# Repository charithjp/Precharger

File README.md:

# Precharger

This project will be a simple DC bus precharger for a 60V DC bus, controlled by an Arduino Nano. Detailed specs to follow.

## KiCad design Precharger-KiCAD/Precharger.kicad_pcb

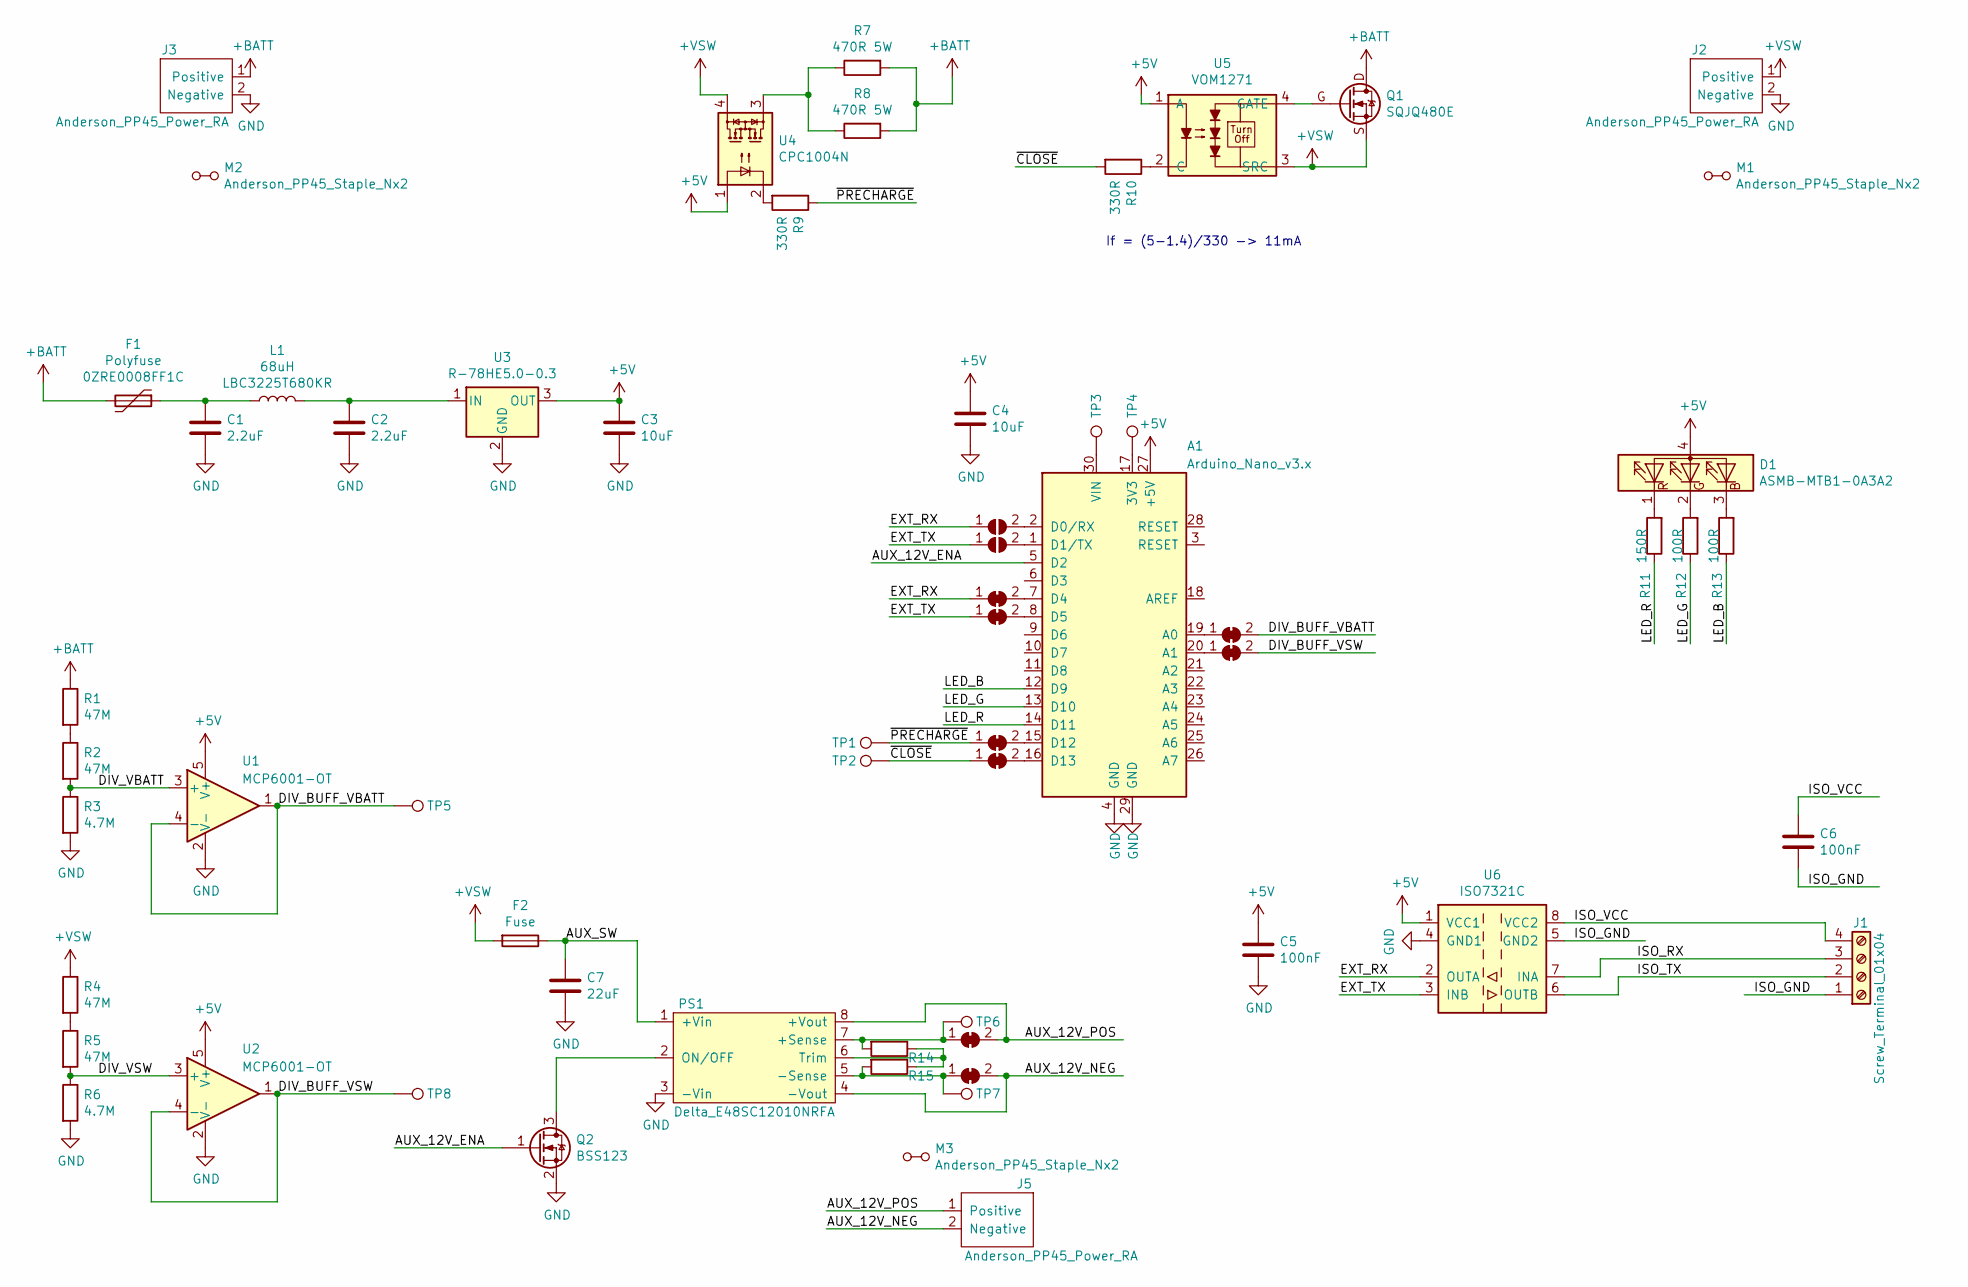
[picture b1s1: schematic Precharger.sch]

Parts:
A1: Arduino_Nano_v3.x; Arduino_Nano
C1, C2: 2.2uF; C_1210_3225Metric_Pad1.42x2.65mm_HandSolder
C3, C4: 10uF; C_0805_2012Metric_Pad1.15x1.40mm_HandSolder
C5, C6: 100nF; C_0805_2012Metric_Pad1.15x1.40mm_HandSolder
C7: 22uF; CP_Radial_D10.0mm_P5.00mm; Digikey PN 399-16572-ND
D1: ASMB-MTB1-0A3A2; LED_Avago_PLCC4_3.2x2.8mm_CW
F1: Polyfuse; Fuse_BelFuse_0ZRE0008FF_L8.3mm_W3.8mm; MFG_PN 0ZRE0008FF1C
F2: Fuse; Fuseholder_Clip-5x20mm_Schurter_0751_0052_Horizontal_Open
J1: Screw_Terminal_01x04; TerminalBlock_Phoenix_PT-1,5-4-3.5-H_1x04_P3.50mm_Horizontal
J2, J3, J5: Anderson_PP45_Power_RA; Anderson_Powerpole-45A-RA-Bottom-Pair
JP1, JP2: SolderJumper_2_Open; SolderJumper-2_P1.3mm_Open_RoundedPad1.0x1.5mm
JP3, JP4, JP5, JP6, JP7, JP8, JP9, JP10: SolderJumper_2_Bridged; SolderJumper-2_P1.3mm_Bridged2Bar_RoundedPad1.0x1.5mm
L1: 68uH; L_1210_3225Metric_Pad1.42x2.65mm_HandSolder; MFG_PN LBC3225T680KR
M1, M2, M3: Anderson_PP45_Staple_Nx2; Anderson_Powerpole-staple-Nx2
PS1: Delta_E48SC12010NRFA; Converter_DCDC_Delta_E48SC12010_THT
Q1: SQJQ480E; Vishay_PowerPAK_8x8L_Single
Q2: BSS123; SOT-23
R1, R2, R4, R5: 47M; R_0805_2012Metric_Pad1.15x1.40mm_HandSolder
R3, R6: 4.7M; R_0805_2012Metric_Pad1.15x1.40mm_HandSolder
R7, R8: 470R 5W; R_Axial_Power_L25.0mm_W9.0mm_P30.48mm
R9, R10: 330R; R_0805_2012Metric_Pad1.15x1.40mm_HandSolder
R11: 150R; R_0805_2012Metric_Pad1.15x1.40mm_HandSolder
R12, R13: 100R; R_0805_2012Metric_Pad1.15x1.40mm_HandSolder
R14, R15: TRIM_UP; R_0805_2012Metric_Pad1.15x1.40mm_HandSolder
TP1, TP2, TP3, TP4, TP5, TP6, TP7, TP8: TestPoint; TestPoint_Keystone_5010-5014_Multipurpose
U1, U2: MCP6001-OT; SOT-23-5_HandSoldering
U3: R-78HE5.0-0.3; Converter_DCDC_RECOM_R-78HB-0.5_THT
U4: CPC1004N; SOP-4_3.8x4.1mm_P2.54mm_CPC1004N
U5: VOM1271; SOP-4_4.57x4.92mm_P2.54mm_VOM1271
U6: ISO7321C; SOIC-8_3.9x4.9mm_P1.27mm

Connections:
+5V: A1.27 (+5V), C3.1, C4.1, C5.1, D1.4 (A), U1.5 (V+), U2.5 (V+), U3.3 (OUT), U4.1, U5.1 (A), U6.1 (VCC1)
+BATT: F1.2, J3.1 (Positive), Q1.D (Drain), R1.1, R7.2, R8.2
+VSW: F2.2, J2.1 (Positive), Q1.S (Source), R4.1, U4.4, U5.3 (SRC)
/AUX_12V_ENA: A1.5 (D2), Q2.1 (G)
/AUX_12V_NEG: J5.2 (Negative), JP10.2 (B), PS1.4 (-Vout)
/AUX_12V_POS: J5.1 (Positive), JP9.2 (B), PS1.8 (+Vout)
/AUX_SW: C7.1, F2.1, PS1.1 (+Vin)
/DIV_BUFF_VBATT: JP7.2 (B), TP5.1, U1.1, U1.4 (-)
/DIV_BUFF_VSW: JP8.2 (B), TP8.1, U2.1, U2.4 (-)
/DIV_VBATT: R2.2, R3.1, U1.3 (+)
/DIV_VSW: R5.2, R6.1, U2.3 (+)
/EXT_RX: JP1.1 (A), JP3.1 (A), U6.2 (OUTA)
/EXT_TX: JP2.1 (A), JP4.1 (A), U6.3 (INB)
/ISO_GND: C6.2, J1.1, U6.5 (GND2)
/ISO_RX: J1.3, U6.7 (INA)
/ISO_TX: J1.2, U6.6 (OUTB)
/ISO_VCC: C6.1, J1.4, U6.8 (VCC2)
/LED_B: A1.12 (D9), R13.1
/LED_G: A1.13 (D10), R12.1
/LED_R: A1.14 (D11), R11.1
/~CLOSE: JP6.1 (A), R10.2, TP2.1
/~PRECHARGE: JP5.1 (A), R9.1, TP1.1
GND: A1.4 (GND), A1.29 (GND), C1.2, C2.2, C3.2, C4.2, C5.2, C7.2, J2.2 (Negative), J3.2 (Negative), PS1.3 (-Vin), Q2.2 (S), R3.2, R6.2, U1.2 (V-), U2.2 (V-), U3.2 (GND), U6.4 (GND1)
unnamed: A1.1 (D1/TX), JP2.2 (B)
unnamed: A1.2 (D0/RX), JP1.2 (B)
unnamed: A1.7 (D4), JP3.2 (B)
unnamed: A1.8 (D5), JP4.2 (B)
unnamed: A1.15 (D12), JP5.2 (B)
unnamed: A1.16 (D13), JP6.2 (B)
unnamed: A1.17 (3V3), TP4.1
unnamed: A1.19 (A0), JP7.1 (A)
unnamed: A1.20 (A1), JP8.1 (A)
unnamed: A1.30 (VIN), TP3.1
unnamed: C1.1, F1.1, L1.1
unnamed: C2.1, L1.2, U3.1 (IN)
unnamed: D1.1 (RK), R11.2
unnamed: D1.2 (GK), R12.2
unnamed: D1.3 (BK), R13.2
unnamed: JP9.1 (A), PS1.7 (+Sense), R14.2, TP6.1
unnamed: JP10.1 (A), PS1.5 (-Sense), R15.2, TP7.1
unnamed: PS1.2 (ON/OFF), Q2.3 (D)
unnamed: PS1.6 (Trim), R14.1, R15.1
unnamed: Q1.G (Gate), U5.4 (GATE)
unnamed: R1.2, R2.1
unnamed: R4.2, R5.1
unnamed: R7.1, R8.1, U4.3
unnamed: R9.2, U4.2
unnamed: R10.1, U5.2 (C)

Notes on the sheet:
If = (5-1.4)/330 -> 11mA

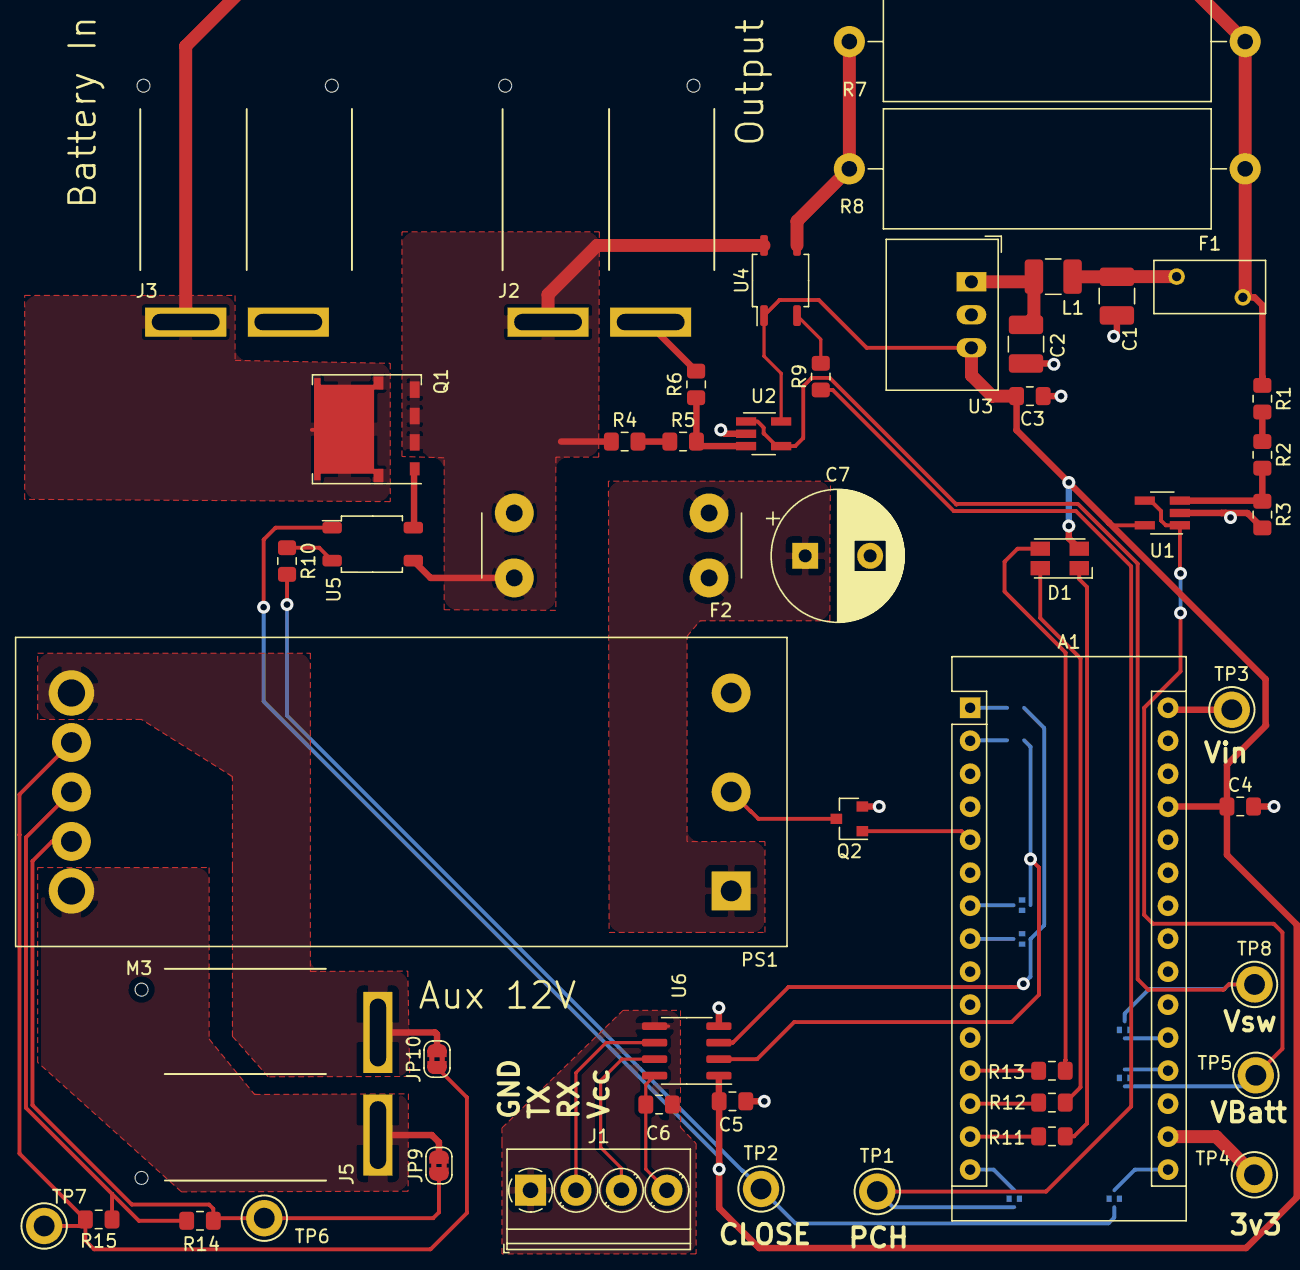
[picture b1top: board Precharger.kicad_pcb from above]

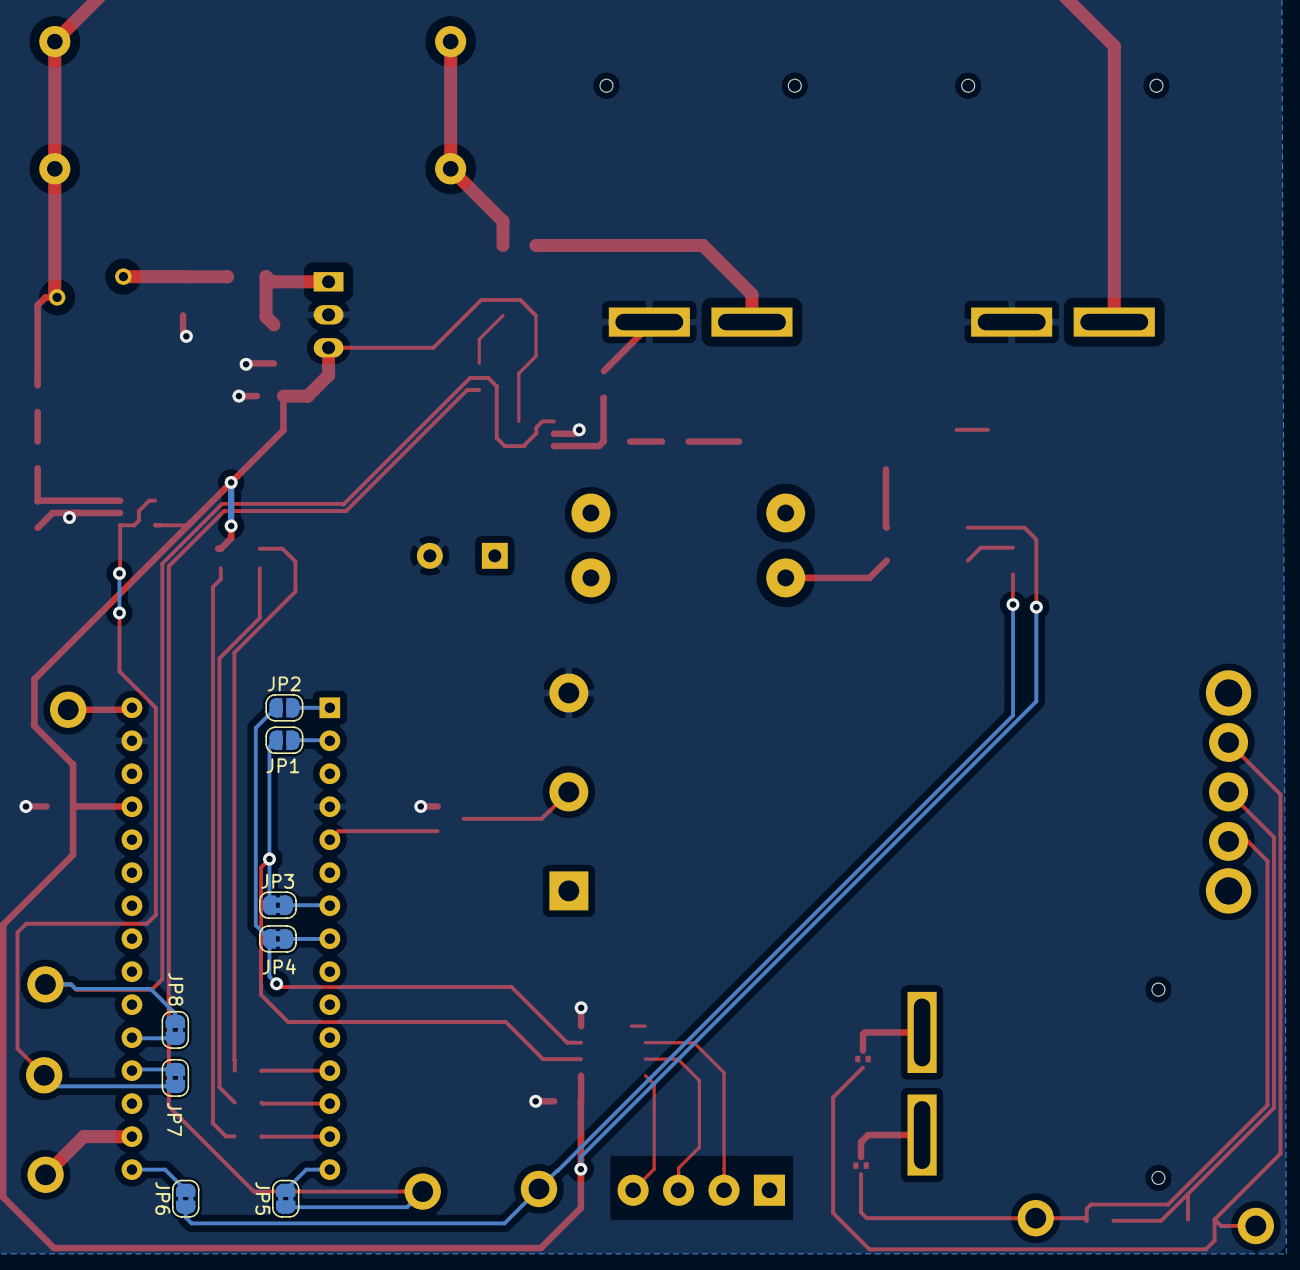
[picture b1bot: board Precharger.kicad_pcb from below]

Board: 2 copper layers, 61 parts (8 on the bottom side), 48 nets.

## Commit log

2019-12-02 Adding precharger library and update to precharger schematics
2019-12-03 Adding two SOP packages
2019-12-03 no message
2019-12-03 Making a start on the PCB
2019-12-05 Continuing
2019-12-06 Daily updates
2019-12-07 Close to finishing up schematic
2019-12-08 Finished routing and generated fab outputs
2019-12-09 Changing dividing resistors down due to reasonably cheap values in 1% tolerence and adding BOM excel file for Digikey Ordering
2019-12-20 Updating errors
2019-12-20 Adding initial sketch
2019-12-21 Working on arduino code
2019-12-21 Working on state machine
2019-12-25 Changed to unsigned printing - still has a slight issue where it starts with the close fet asserted :(
2019-12-26 Getting a v2 going to try a buck precharge stage
2019-12-26 Converted v2 to multi sheet schematics
2020-01-11 Starting update with negative switching
2020-01-11 Adding comment for inductor
2020-01-22 Testing out TINA-Ti for simulation.
2020-01-30 More datasheets!
